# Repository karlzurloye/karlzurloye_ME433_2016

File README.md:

Karl zur Loye

April 4, 2016

Northwestern ME 433 course code

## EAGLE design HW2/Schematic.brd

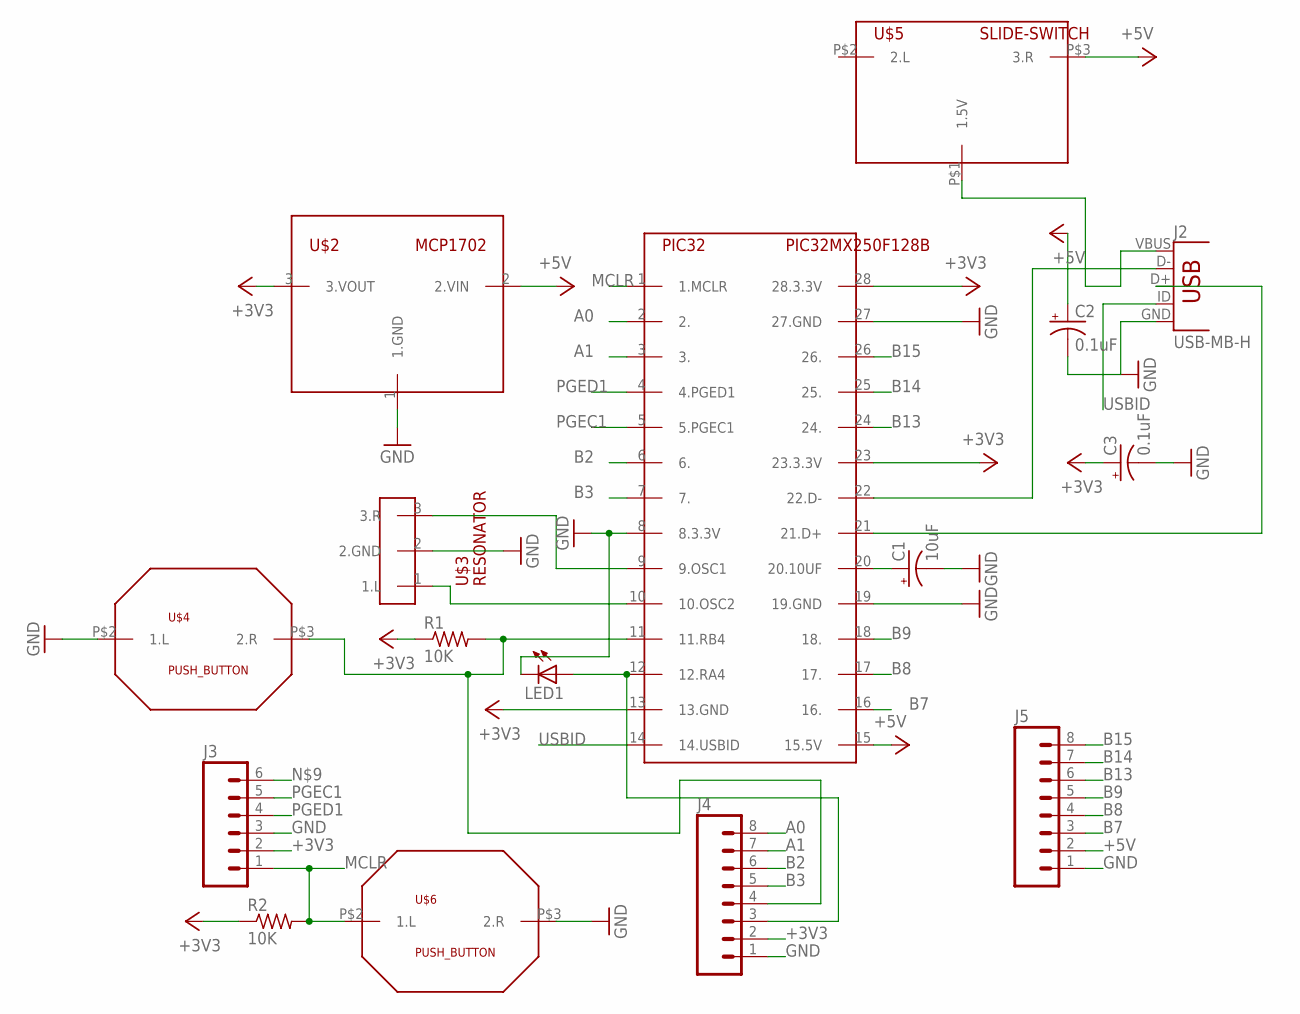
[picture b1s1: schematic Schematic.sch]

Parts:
C1: 10uF; E2,5-5
C2, C3: 0.1uF; E2,5-5
J2: USB-MB-H
J3: M06SILK_FEMALE_PTH; 1X06
J4, J5: M08SILK_FEMALE_PTH; 1X08
LED1: LED3MM
PIC32: PIC32MX250F128B; DIL28-3
R1, R2: 10K; 0207/10
U$2: MCP1702; TO92
U$3: RESONATOR; 1X03
U$4, U$6: PUSH_BUTTON
U$5: SLIDE-SWITCH

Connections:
+3V3: C3.+, J3.2, J4.2, PIC32.13 (13.GND), PIC32.23 (23.3.3V), PIC32.28 (28.3.3V), R1.1, R2.1, U$2.3 (3.VOUT)
+5V: C2.+, J5.2, PIC32.15 (15.5V), U$2.2 (2.VIN), U$5.P$3 (3.R)
A0: J4.8, PIC32.2 (2.)
A1: J4.7, PIC32.3 (3.)
A4: J4.3, LED1.A, PIC32.12 (12.RA4)
B2: J4.6, PIC32.6 (6.)
B3: J4.5, PIC32.7 (7.)
B4: J4.4, PIC32.11 (11.RB4), R1.2, U$4.P$3 (2.R)
B7: J5.3, PIC32.16 (16.)
B8: J5.4, PIC32.17 (17.)
B9: J5.5, PIC32.18 (18.)
B13: J5.6, PIC32.24 (24.)
B14: J5.7, PIC32.25 (25.)
B15: J5.8, PIC32.26 (26.)
GND: C1.-, C2.-, C3.-, J2.GND (1.GND), J3.3, J4.1, J5.1, LED1.K (C), PIC32.8 (8.3.3V), PIC32.19 (19.GND), PIC32.27 (27.GND), U$2.1 (1.GND), U$3.2 (2.GND), U$4.P$2 (1.L), U$6.P$3 (2.R)
MCLR: J3.1, PIC32.1 (1.MCLR), R2.2, U$6.P$2 (1.L)
unnamed: C1.+, PIC32.20 (20.10UF)
unnamed: J2.D- (4.D-), PIC32.22 (22.D-)
unnamed: J2.D+ (3.D+), PIC32.21 (21.D+)
unnamed: PIC32.9 (9.OSC1), U$3.3 (3.R)
unnamed: PIC32.10 (10.OSC2), U$3.1 (1.L)
unnamed: J2.VBUS (5.VBUS), U$5.P$1 (1.5V)
PGEC1: J3.5, PIC32.5 (5.PGEC1)
PGED1: J3.4, PIC32.4 (4.PGED1)
USBID: J2.ID (2.ID), PIC32.14 (14.USBID)

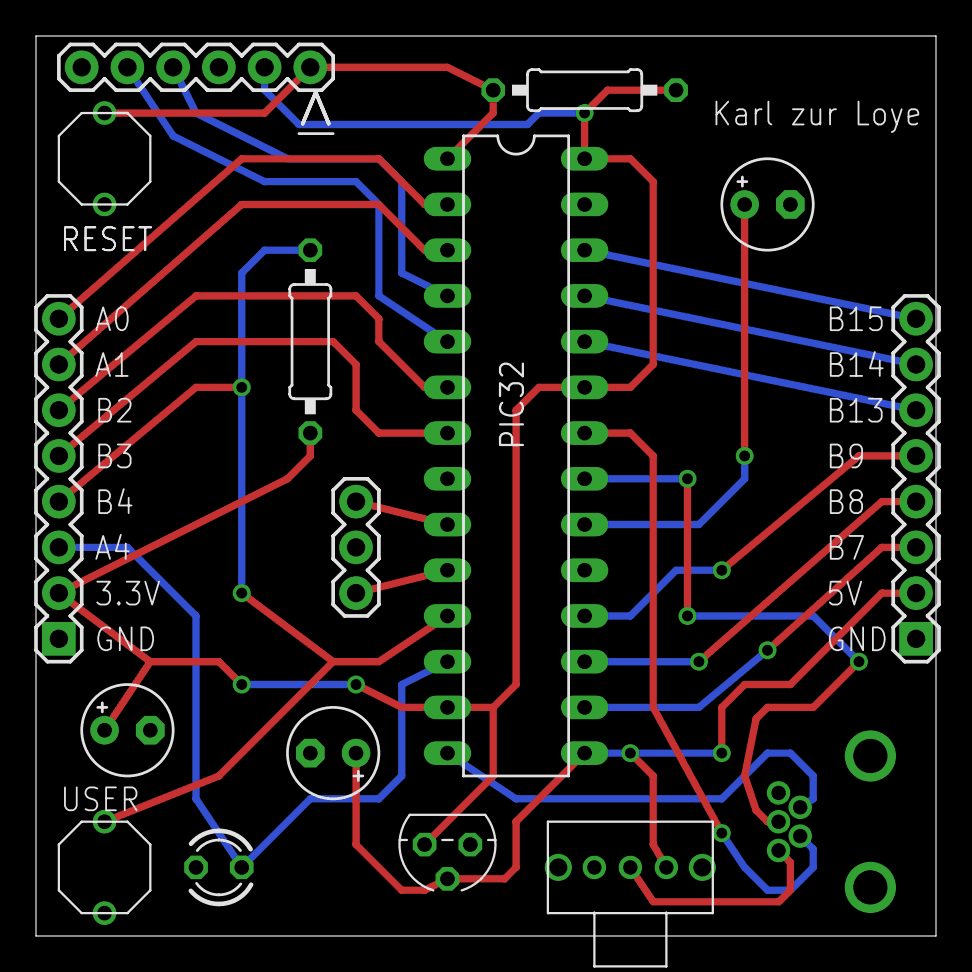
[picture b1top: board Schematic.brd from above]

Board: 2 copper layers, 50.0 x 50.0 mm, 16 parts (0 on the bottom side), 25 nets.

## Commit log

2016-04-05 My first commit!
2016-04-05 basic edits
2016-04-05 added circuit diagram
2016-04-05 oscilloscope reading and final circuit
2016-04-05 code template
2016-04-05 mplab files
2016-04-05 #pragma complete (untested)
2016-04-05 fixed code (still not done can't get pic kit to work)
2016-04-05 code works now!
2016-04-07 added eagle
2016-04-07 completed library!
2016-04-11 library finished and schematic started
2016-04-12 schematic done
2016-04-12 board complete!
2016-04-12 pcb updated
2016-04-12 gerber files complete! PCB ready for printing
2016-04-12 tbh not sure what changed
2016-04-26 spi complete!
2016-04-26 spi with oscilloscope screenshot
2016-04-26 i2c almost done!
2016-04-26 I2C complete!
2016-04-26 i2c with picture!
2016-04-28 almost done with imu!
2016-04-29 emu complete with oscilloscope screenshots!
2016-05-10 LCD string printing works!
2016-05-25 hw5 done!!
2016-06-04 tidying up
2016-06-05 basic camera app complete!
2016-06-05 wheel complete!
2016-06-06 laser cut box designed
2016-06-06 robot dxfs done!
2016-06-08 so many updates my b
2016-06-08 HID Mouse complete!
2016-06-08 PIC CDC Complete!
2016-06-08 Uploaded Box Pictures!
2016-06-08 Wheel picture uploaded!
2016-06-08 laser cutting robot pictures uploaded!
2016-06-08 line tracker pictures uploaded!
2016-06-08 robot pics uploaded!
2016-06-08 final code for pic racer
2016-06-08 included hello world app picture
